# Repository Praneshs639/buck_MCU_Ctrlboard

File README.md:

Buck MCU Control Board
Overview

Microcontroller-based Buck Converter Control Board designed for efficient DC-DC step-down power regulation. 
This PCB provides stable voltage output, precise switching control, and reliable performance for embedded systems and low-power electronics applications.

The design have lot of space and some error, although through this design i have learned some techniques and way to design a PCB with reducing the error and spacing .

Features

High-efficiency buck converter topology

Microcontroller-based control

Stable regulated output voltage

Optimized PCB layout for power integrity

Low noise and thermal-aware design

Suitable for embedded and IoT applications

Applications

Embedded systems power supply

IoT devices

Battery-powered electronics

Robotics and automation projects

Portable electronic systems

Design Files Included

KiCad schematic files

PCB layout files

Project files

Bill of Materials (BOM)

Board images

Tools Used

KiCad (PCB Design)

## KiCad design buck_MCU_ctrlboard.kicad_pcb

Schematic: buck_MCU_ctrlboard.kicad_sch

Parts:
C1: 10uF; C_0402_1005Metric_Pad0.74x0.62mm_HandSolder
C2, C6, C9: 0.1uF; C_0201_0603Metric_Pad0.64x0.40mm_HandSolder
C3: 22uf; C_0603_1608Metric_Pad1.08x0.95mm_HandSolder
C4: 10uf; C_0603_1608Metric_Pad1.08x0.95mm_HandSolder
C5: 0.1uF; C_0603_1608Metric_Pad1.08x0.95mm_HandSolder
C7: 330uF/50v; CP_Elec_3x5.4
C8, C10: 1uF; C_0402_1005Metric
C11: 330uF/25V; CP_Elec_3x5.4
C12: 33nF; C_0402_1005Metric
D1: 12v; D_1206_3216Metric_Pad1.42x1.75mm_HandSolder
D2: red; LED_0201_0603Metric
D3: MBRD1045G; D_0603_1608Metric_Pad1.05x0.95mm_HandSolder
D4, D5: red; LED_0201_0603Metric_Pad0.64x0.40mm_HandSolder
J1: Conn_01x18_Male; PinSocket_1x18_P1.00mm_Vertical
J2: Conn_01x14_Male; PinSocket_1x14_P1.00mm_Vertical
J18: Conn_01x05_Male; Hirose_DF13-05P-1.25DSA_1x05_P1.25mm_Vertical
L1: 47uH/5A; L_Axial_L5.3mm_D2.2mm_P7.62mm_Horizontal_Vishay_IM-1
Q1: Q_PMOS_GDS; SOT-23W
R1: 10k; R_1206_3216Metric_Pad1.30x1.75mm_HandSolder
R2, R3, R4, R5: 10k; R_2010_5025Metric
R6: 500; R_0603_1608Metric_Pad0.98x0.95mm_HandSolder
R7: 10K; R_2010_5025Metric_Pad1.40x2.65mm_HandSolder
R8: 1K; R_2010_5025Metric_Pad1.40x2.65mm_HandSolder
R9: 500; R_0805_2012Metric
R10: 65 R; R_0805_2012Metric
SW1: reset; SW_PUSH_6mm_H4.3mm
SW2: boot; SW_PUSH_6mm_H4.3mm
TP1: + BAT -; TestPoint_2Pads_Pitch5.08mm_Drill1.3mm
U1: LT1762-3; MSOP-8_3x3mm_P0.65mm
U2: ESP32-S2-WROVER-I; My_Project.pretty
U3: buck ic; CONV_XL4015; PARTREV 1.5
trim1: R_Potentiometer_Trim_US; Potentiometer_Bourns_3214X_Vertical

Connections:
/GPIO 16: J1.13, U2.16 (IO13)
/GPIO_1: J1.1, U2.4 (IO01)
/GPIO_2: J1.2, U2.5 (IO02)
/GPIO_3: J1.3, U2.6 (IO03)
/GPIO_4: J1.4, U2.7 (IO04)
/GPIO_5: J1.5, U2.8 (IO05)
/GPIO_6: J1.6, U2.9 (IO06)
/GPIO_7: J1.7, U2.10 (IO07)
/GPIO_8: J1.8, U2.11 (IO08)
/GPIO_9: J1.9, U2.12 (IO09)
/GPIO_10: J1.10, U2.13 (IO10)
/GPIO_11: J1.11, U2.14 (IO11)
/GPIO_12: J1.12, U2.15 (IO12)
/GPIO_14: J1.14, U2.17 (IO14)
/GPIO_15: J1.15, U2.18 (IO15)
/GPIO_16: J1.16, U2.19 (IO16)
/GPIO_17: J1.17, U2.20 (IO17)
/GPIO_18: J1.18, U2.21 (IO18)
/GPIO_21: J2.1, U2.24 (IO21)
/GPIO_26: J2.2, U2.25 (IO26)
/GPIO_33: J2.3, U2.27 (IO33)
/GPIO_34: J2.4, U2.28 (IO34)
/GPIO_35: J2.5, U2.29 (IO35)
/GPIO_36: J2.6, U2.30 (IO36)
/GPIO_37: J2.7, U2.31 (IO37)
/GPIO_38: J2.8, U2.32 (IO38)
/GPIO_39: J2.9, U2.33 (IO39)
/GPIO_40: J2.10, U2.34 (IO40)
/GPIO_41: J2.11, U2.35 (IO41)
/GPIO_42: J2.12, U2.36 (IO42)
/GPIO_RX: J2.14, U2.38 (RXD0)
/GPIO_TX: J2.13, U2.37 (TXD0)
/Vout: C1.1, C10.1, C11.1, C12.1, J18.1, J18.2, J18.3, J18.4, J18.5, L1.2, R7.1, R9.1, U1.5 (~SHDN), U1.8 (IN)
/out: C7.1, C8.1, C9.1, Q1.2 (D), R6.1, U3.5 (VIN)
GND: C1.2, C3.2, C4.2, C5.2, C6.2, C7.2, C8.2, C10.2, C11.2, D2.1 (K), D3.2 (A), D4.1 (K), D5.1 (K), R4.2, R5.2, R8.2, SW1.1, SW2.2, TP1.2, U1.4 (GND), U2.1 (GND), U2.26 (GND), U2.42 (GND), U2.43 (GND), U3.1 (GND), trim1.3
unnamed: D1.2 (A), Q1.1 (G), R1.2
unnamed: D2.2 (A), R6.2
unnamed: D3.1 (K), L1.1, U3.3 (SW), U3.3.1 (SW)
unnamed: D4.2 (A), R9.2
unnamed: D5.2 (A), R10.1
unnamed: R8.1, trim1.2
unnamed: C2.2, U1.3 (BYP)
unnamed: C2.1, C3.1, C4.1, C5.1, R2.1, R3.1, R10.2, U1.1 (OUT), U1.2 (SENSE), U2.2 (3V3)
unnamed: C6.1, R2.2, SW1.2, U2.41 (EN)
unnamed: R3.2, SW2.1, U2.3 (IO00)
unnamed: R5.1, U2.39 (IO45)
unnamed: R4.1, U2.40 (IO46)
unnamed: C12.2, R7.2, U3.2 (FB), trim1.1
unnamed: C9.2, U3.4 (VC)
VCC: D1.1 (K), Q1.3 (S), R1.1, TP1.1

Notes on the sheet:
SUPPLY
CONTROL UNIT
REVERSE POLARTIY PROTECTIOIN
BCUK CONVERTER

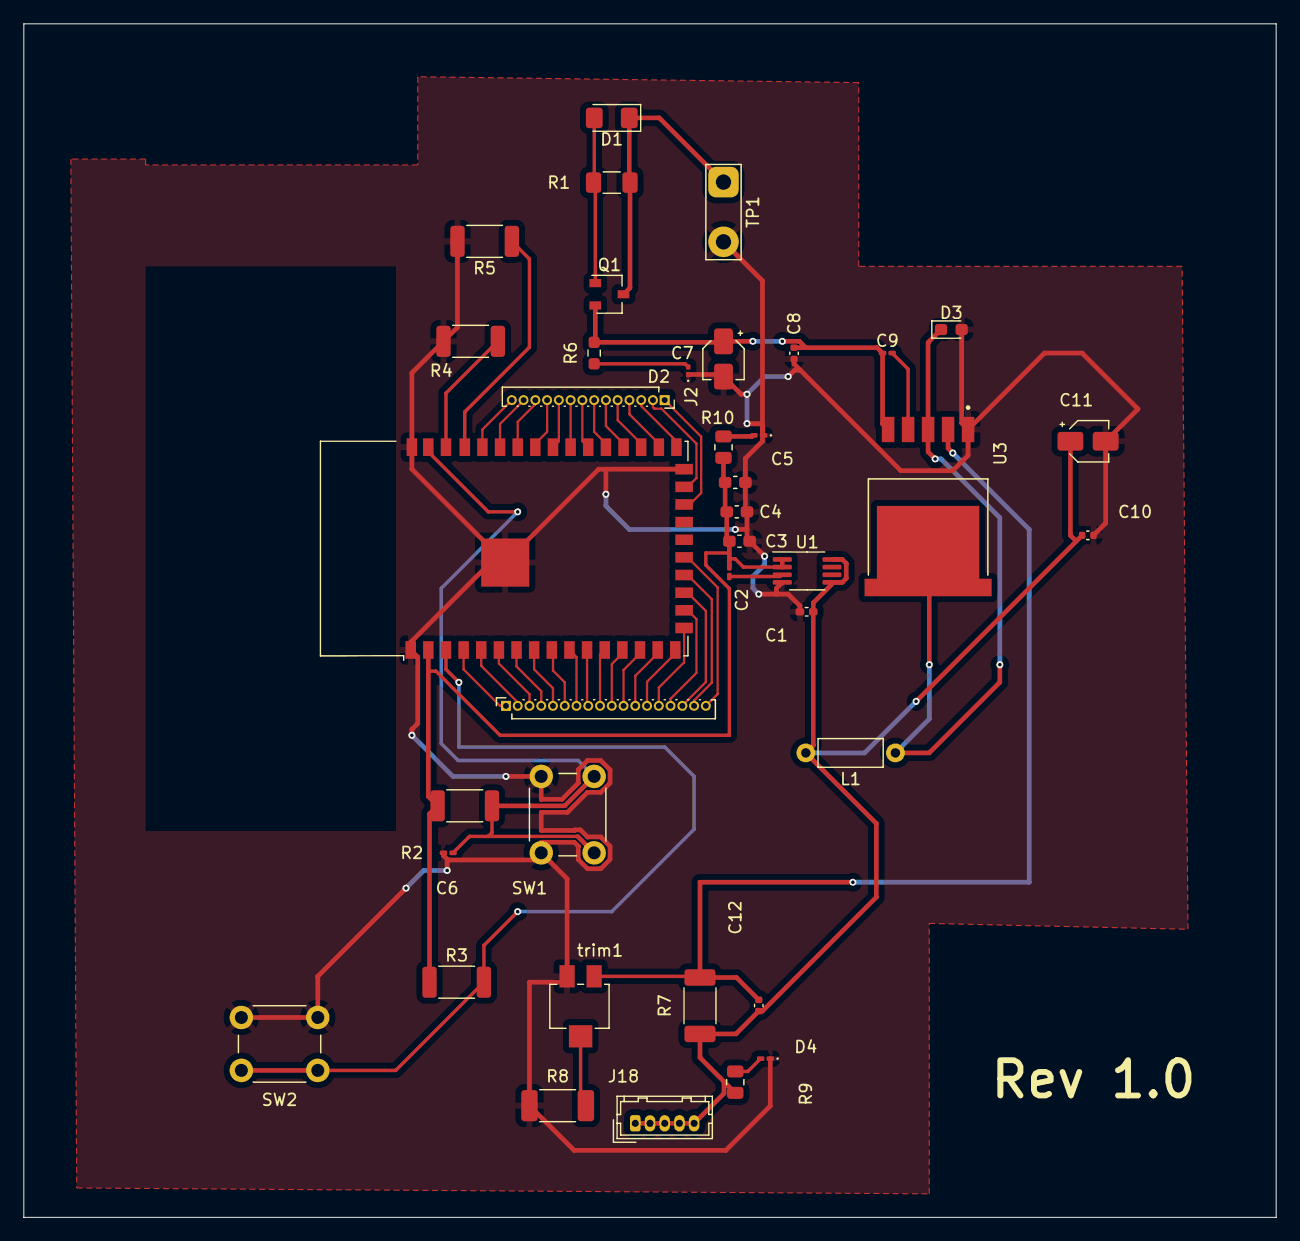
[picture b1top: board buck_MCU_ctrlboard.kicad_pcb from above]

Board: 2 copper layers, 106.5 x 101.5 mm, 39 parts (0 on the bottom side), 50 nets.

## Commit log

2026-02-18 Initial upload of Buck MCU Control Board PCB files
2026-02-18 Add README for Buck MCU Control Board
    Added detailed overview, features, applications, design files, tools used, author information, and license for the Buck MCU Control Board.
